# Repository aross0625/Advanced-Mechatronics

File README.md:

# Advanced-Mechatronics
Collection of coursework-related programs for the Advanced Mechatronics (ME 433) course at Northwestern University

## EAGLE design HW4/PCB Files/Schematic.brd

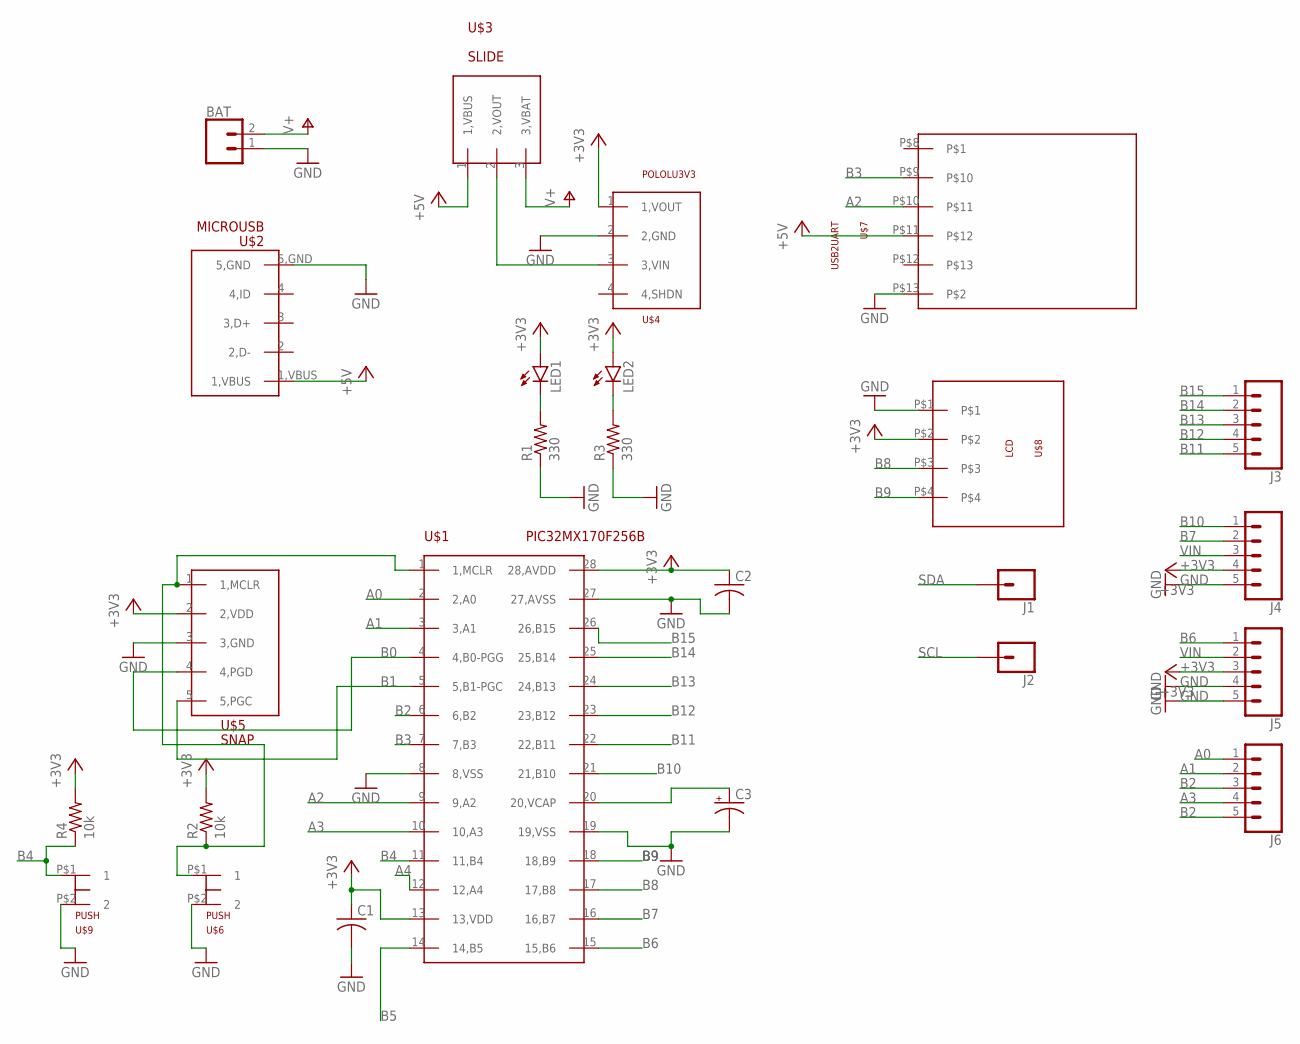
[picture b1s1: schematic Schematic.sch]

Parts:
BAT: CONN_02; 1X02
C1, C2: C-US025-030X050; C025-030X050
C3: CPOL-USB45181B; B45181B
J1, J2: CONN_01; 1X01
J3, J4, J5, J6: CONN_05; 1X05
LED1, LED2: LED3MM
R1, R3: 330; 0207/10
R2, R4: 10k; 0207/10
U$1: PIC32MX170F256B; DIL28-3
U$2: MICROUSB
U$3: SLIDE
U$4: POLOLU3V3
U$5: SNAP
U$6, U$9: PUSH
U$7: USB2UART
U$8: LCD

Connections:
+3V3: C1.1, C2.1, J4.4, J5.3, LED1.A, LED2.A, R2.2, R4.2, U$1.13 (13,VDD), U$1.28 (28,AVDD), U$4.1 (1,VOUT), U$5.2 (2,VDD), U$8.P$2
+5V: U$2.1,VBUS, U$3.1 (1,VBUS), U$7.P$11
A0: J6.1, U$1.2 (2,A0)
A1: J6.2, U$1.3 (3,A1)
A2: U$1.9 (9,A2), U$7.P$10
A3: J6.4, U$1.10 (10,A3)
A4: U$1.12 (12,A4)
B0: U$1.4 (4,B0-PGG), U$5.4 (4,PGD)
B1: U$1.5 (5,B1-PGC), U$5.5 (5,PGC)
B2: J6.3, J6.5, U$1.6 (6,B2)
B3: U$1.7 (7,B3), U$7.P$9
B4: R4.1, U$1.11 (11,B4), U$9.P$1 (1)
B5: U$1.14 (14,B5)
B6: J5.1, U$1.15 (15,B6)
B7: J4.2, U$1.16 (16,B7)
B8: U$1.17 (17,B8), U$8.P$3
B9: U$1.18 (18,B9), U$8.P$4
B10: J4.1, U$1.21 (21,B10)
B11: J3.5, U$1.22 (22,B11)
B12: J3.4, U$1.23 (23,B12)
B13: J3.3, U$1.24 (24,B13)
B14: J3.2, U$1.25 (25,B14)
B15: J3.1, U$1.26 (26,B15)
GND: BAT.1, C1.2, C2.2, C3.-, J4.5, J5.4, J5.5, R1.1, R3.1, U$1.8 (8,VSS), U$1.19 (19,VSS), U$1.27 (27,AVSS), U$2.5,GND, U$4.2 (2,GND), U$5.3 (3,GND), U$6.P$2 (2), U$7.P$13, U$8.P$1, U$9.P$2 (2)
unnamed: U$3.2 (2,VOUT), U$4.3 (3,VIN)
unnamed: LED1.K (C), R1.2
unnamed: R2.1, U$1.1 (1,MCLR), U$5.1 (1,MCLR), U$6.P$1 (1)
unnamed: LED2.K (C), R3.2
unnamed: C3.+, U$1.20 (20,VCAP)
SCL: J2.1
SDA: J1.1
V+: BAT.2, U$3.3 (3,VBAT)
VIN: J4.3, J5.2

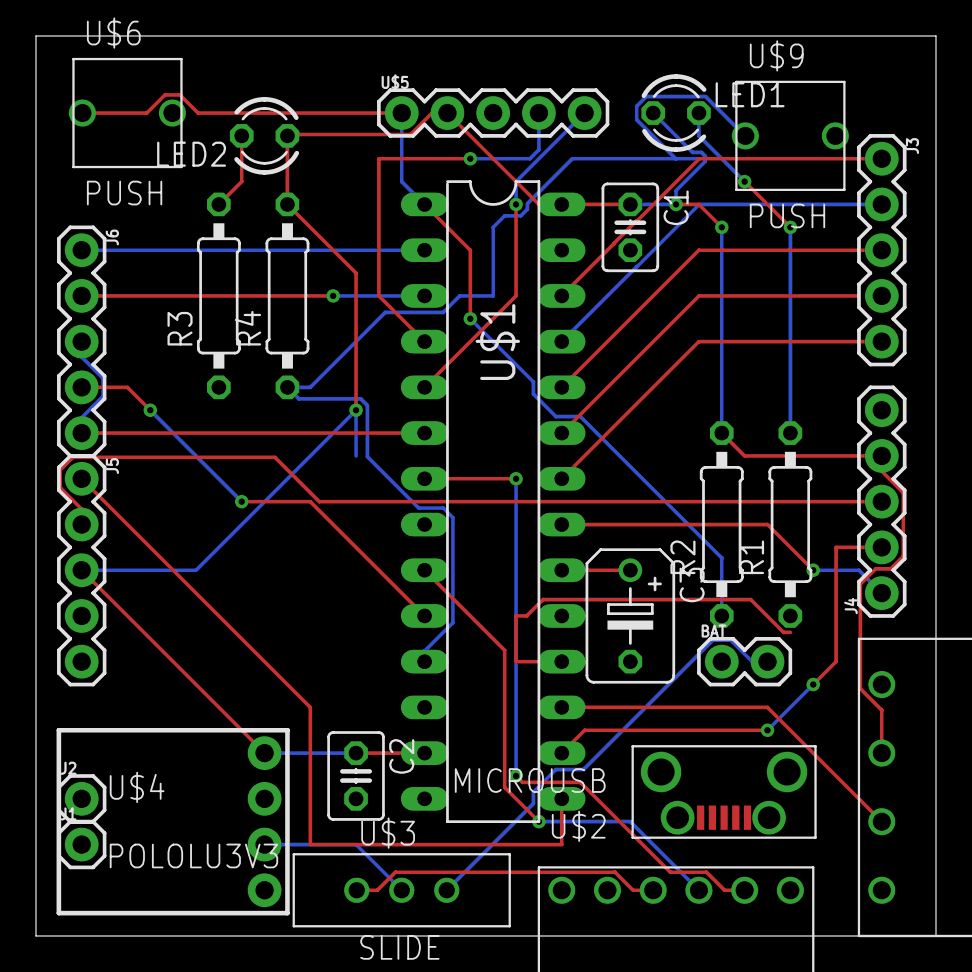
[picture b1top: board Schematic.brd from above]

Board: 2 copper layers, 50.0 x 50.0 mm, 25 parts (0 on the bottom side), 29 nets.

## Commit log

2022-04-04 HW2 V1.0
    Initial Push
2022-04-07 HW3 V1.0
    Initial Push
2022-04-14 HW4 V1
    Initial Push
2022-04-14 HW4 V1.0
    Initial Push
2022-04-21 HW5 V1.0
    Initial Push
2022-04-25 HW6 V1.0
    Initial Push
2022-04-28 HW7 V1.0
    Initial Push
2022-05-04 HW8 V1.0
    Initial Push
2022-05-05 HW9 V1.0
    Initial Push
2022-05-12 HW10 V1.0
    Initial Push
2022-05-12 HW10 V1.1
    Minor Updates
2022-05-21 HW11 V1.0
    Initial Push
2022-06-08 HW9 V1.1
    Edits
2022-06-09 HW7 V1.1
    Edits
2022-06-09 Final Project V1.0
    Initial Push
